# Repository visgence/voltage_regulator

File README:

Voltage Regulator Board
Made with KiCad 4737
Visgence Inc. 2014

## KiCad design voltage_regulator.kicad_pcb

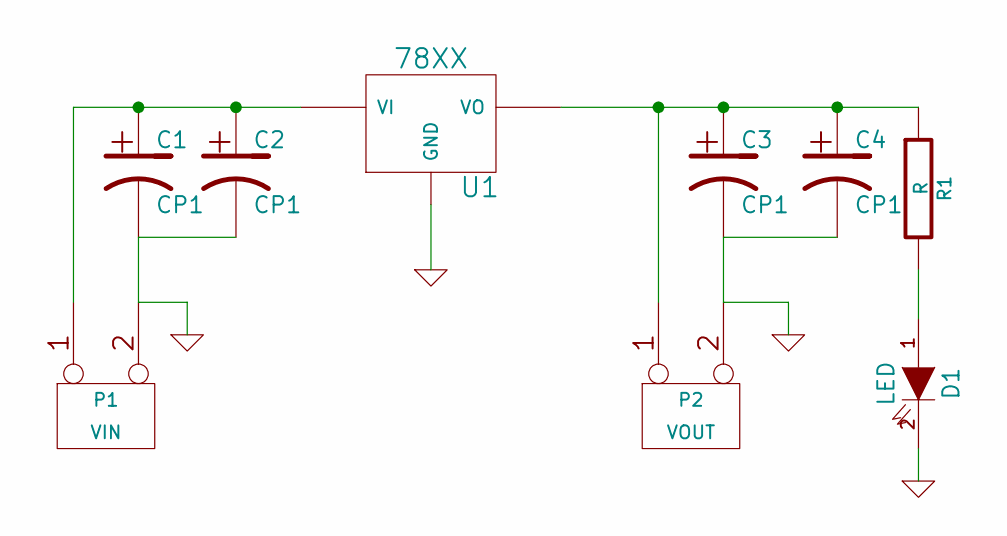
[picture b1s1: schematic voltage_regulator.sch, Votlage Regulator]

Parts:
C1, C2, C3, C4: CP1
D1: LED
P1: VIN
P2: VOUT
R1: R
U1: 78XX

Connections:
GND: C1.2, C2.2, C3.2, C4.2, D1.2 (K), P1.2 (PM), P2.2 (PM), U1.GND
unnamed: C1.1, C2.1, P1.1, U1.VI
unnamed: C3.1, C4.1, P2.1, R1.1, U1.VO
unnamed: D1.1 (A), R1.2

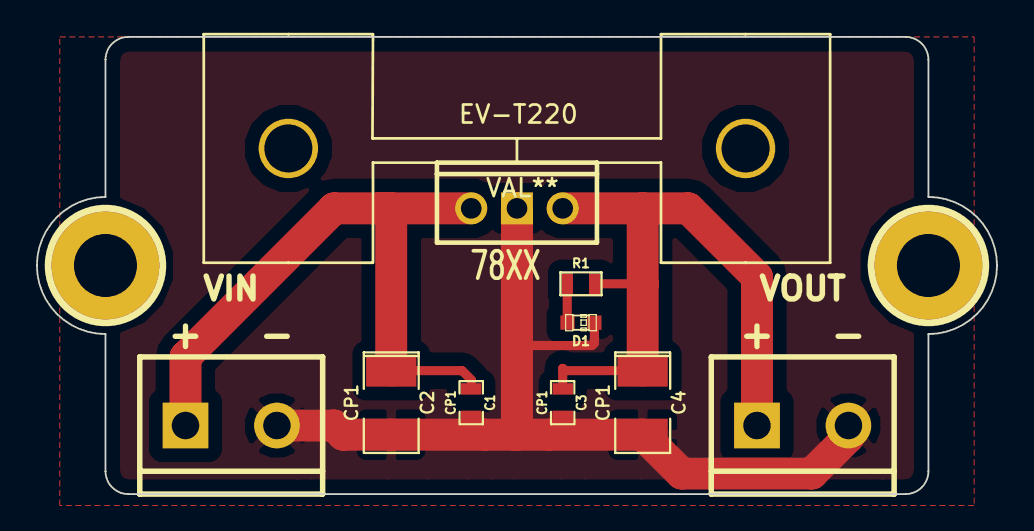
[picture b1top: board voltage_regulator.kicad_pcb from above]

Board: 2 copper layers, 53.3 x 25.4 mm, 12 parts (0 on the bottom side), 4 nets.

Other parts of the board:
EV-T220: VAL**; EV-T220
h1, h2: pin; 1pin_C

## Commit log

2014-03-10 Inital commit
2014-03-10 Added readme with ver number
2014-03-10 Chagned page size
2014-03-10 forgot cmp file
2014-03-10 Fixed year on readme
2016-12-13 Routed on newer kicad
